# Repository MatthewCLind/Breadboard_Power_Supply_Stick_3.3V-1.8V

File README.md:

SparkFun Breadboard Power Supply Stick - 3.3V/1.8V
=====================================

[*SparkFun Breadboard Power Supply Stick - 3.3V/1.8V (PRT-10934)*](https://www.sparkfun.com/products/13157)

This is a simple board that takes a micro USB input and outputs a selectable 1.8V or 3.3V regulated voltage.
All headers are 0.1" pitch for simple insertion into a breadboard. 

Repository Contents
-------------------
* **/Hardware** - All KiCAD and Eagle design files (.brd, .sch, .STL)
* **/Production** - Test bed files and production panel files

Version History
---------------
* [v_14](https://github.com/sparkfun/Breadboard_Power_Supply_Stick_3.3V-1.8V/tree/v_14) GitHub files - version 1.4.  
* [v_10](https://github.com/sparkfun/Breadboard_Power_Supply_Stick_3.3V-1.8V/tree/v_10) GitHub files - version 1.0

License Information
-------------------
The hardware is released under [Creative Commons ShareAlike 4.0 International](https://creativecommons.org/licenses/by-sa/4.0/).

Distributed as-is; no warranty is given.

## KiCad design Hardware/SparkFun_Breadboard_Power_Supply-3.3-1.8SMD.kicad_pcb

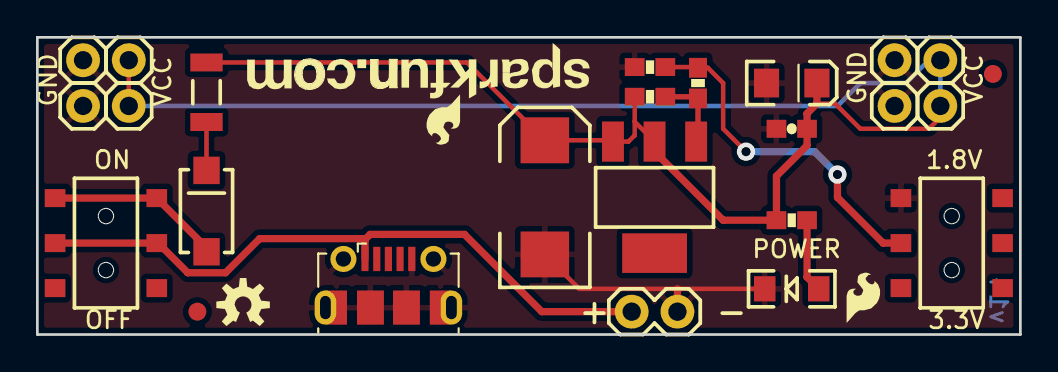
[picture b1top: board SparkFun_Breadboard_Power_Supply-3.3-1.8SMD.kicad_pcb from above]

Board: 2 copper layers, 54.6 x 16.5 mm, 30 parts (0 on the bottom side), 8 nets.

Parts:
C1: 100uF; EIA7343
C2: 10uF; EIA3216
C3: 0.1uF; 0603-CAP
D1: 1N4001; SMA-DIODE-TYLERALT1
F1: PTCSMD-W; PTC-1206-WIDE
FRAME1: FRAME-LETTER; CREATIVE_COMMONS
J1: USB_B_Micro; USB_Micro-B_Molex-105017-0001
JP1, JP2, JP3, JP4, JP6, JP7, JP8, JP9: M01PTH; 1X01
JP5: M02PTH; 1X02
LED2: Power; LED-1206
LOGO1: OSHW-LOGOS; OSHW-LOGO-S
R1, R4: 240; 0603-RES
R3: 287; 0603-RES
S1: On/Off; AYZ0202
S2: Voltage; AYZ0202
U1: V_REG_317SMD; SOT223
U$1: LOGO-SFESK; SFE-LOGO-FLAME
U$2, U$2#2: LOGO-SFENEW; SFE-NEW-WEBLOGO
U$3, U$4: FIDUCIAL1X2; FIDUCIAL-1X2
fR2: 105; 0603-RES

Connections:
/VIN: J1.1, JP5.1, S1.2, S1.5
GND: C1.C, C2.C, C3.2, J1.5, J1.6, JP1.1, JP4.1, JP5.2, JP6.1, JP9.1, LED2.C, R3.1, S2.3
unnamed: D1.A, S1.1, S1.4
unnamed: D1.C, F1.1
unnamed: LED2.A, R4.1
unnamed: R1.1, U1.1, fR2.2
unnamed: R3.2, S2.2, fR2.1
VCC: C1.A, C2.A, C3.1, F1.2, JP2.1, JP3.1, JP7.1, JP8.1, R1.2, R4.2, U1.2, U1.3

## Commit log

2018-09-03 Created KiCAD Files; swapped barrel adapter for USB micro
2018-09-03 Updated README to indicate Micro USB
2018-09-03 updated picture

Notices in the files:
parts and their libraries:
Released under the Creative Commons Attribution Share-Alike 3.0 License
